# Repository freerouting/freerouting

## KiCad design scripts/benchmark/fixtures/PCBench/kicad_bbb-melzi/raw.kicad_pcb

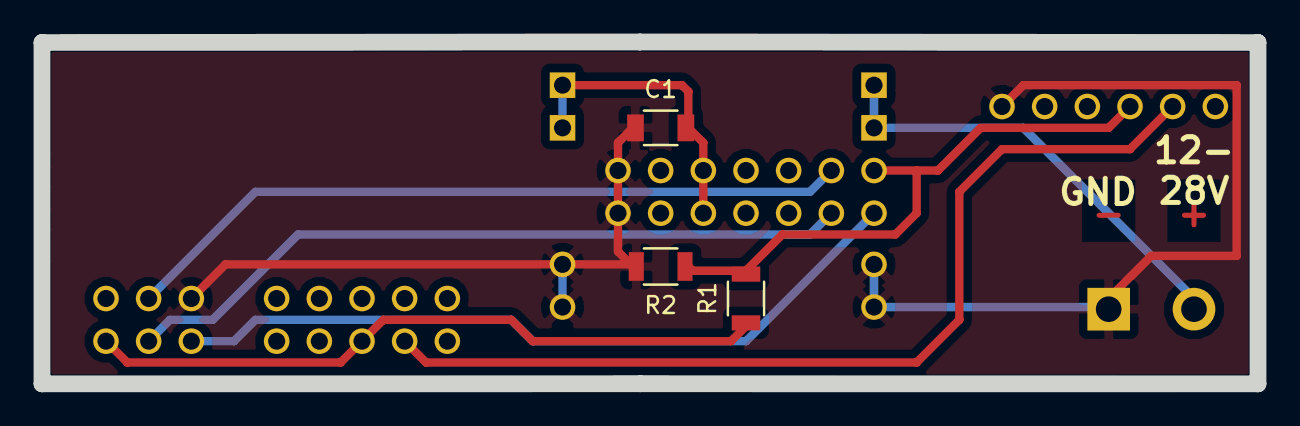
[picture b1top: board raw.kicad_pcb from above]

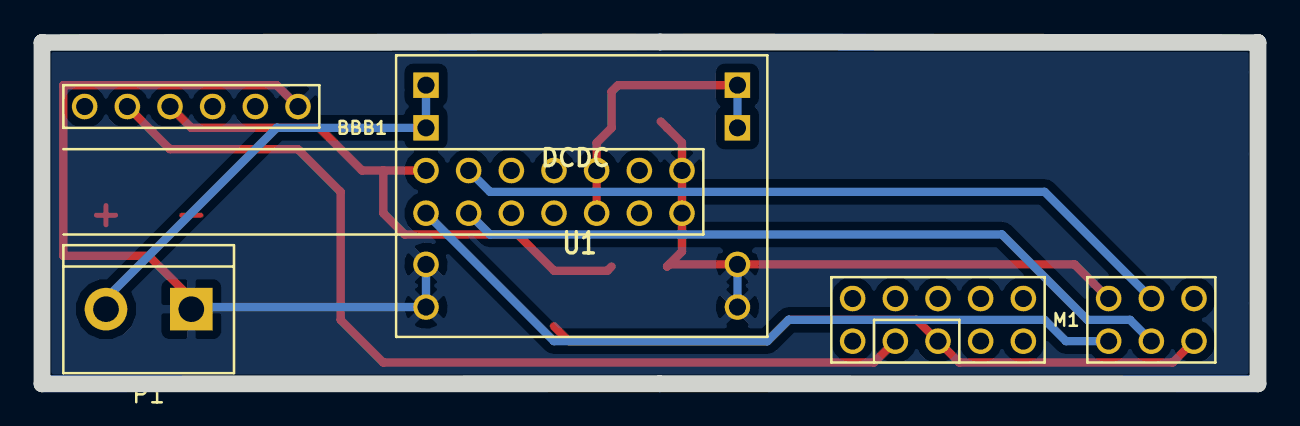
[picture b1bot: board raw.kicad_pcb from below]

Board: 2 copper layers, 72.4 x 20.4 mm, 7 parts (4 on the bottom side), 9 nets.

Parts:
BBB1: BBB
C1: C; C_1206
M1: MELZI; Melzi
P1: CONN_2; bornier2
R1, R2: R; R_1206
U1: DCDC

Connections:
/GND: BBB1.GND, C1.1, M1.GND, P1.1, R2.2, U1.GND, U1.GND2
/MISO: M1.MISO, M1.TxD, R1.1
/MISO3: BBB1.50, BBB1.RxD, R1.2, R2.1
/MOSI: BBB1.60, M1.MOSI
/Reset: BBB1.31, M1.~RST
/SCK: BBB1.30, M1.SCK
/VDD: BBB1.VDD, C1.2, U1.Vout
/VIN: P1.2, U1.Vin
unnamed: BBB1.TxD, M1.RxD

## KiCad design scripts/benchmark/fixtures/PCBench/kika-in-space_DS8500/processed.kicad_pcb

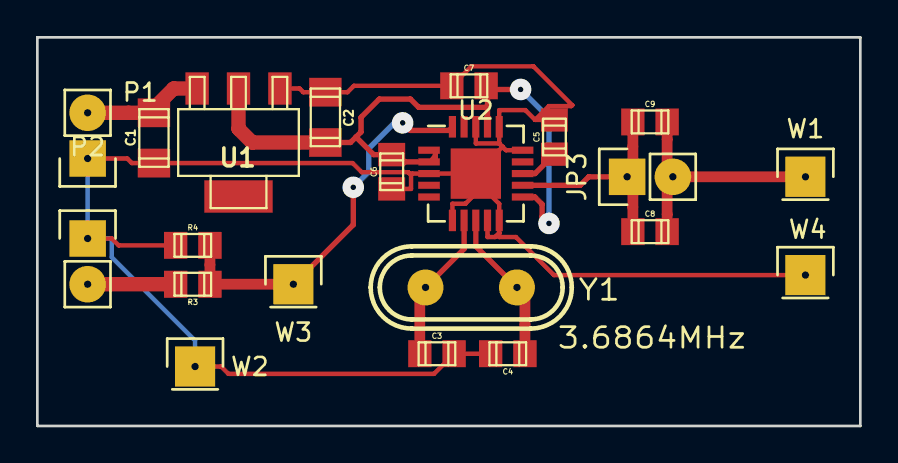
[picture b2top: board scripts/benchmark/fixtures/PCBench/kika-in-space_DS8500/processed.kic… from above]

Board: 2 copper layers, 45.7 x 21.6 mm, 21 parts (0 on the bottom side), 10 nets.

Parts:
C1, C2: 1u; c_1206
C3, C4: 22p; c_0805
C5, C6, C7, C8, C9: 100n; c_0805
JP3: Pin_Header_Straight_1x02
P1: POWER; Pin_Header_Straight_1x02
P2: INTERFACE; Pin_Header_Straight_1x02
R3: 10k; r_0805
R4: 20k; r_0805
U1: AP1117V5; sot223
U2: DS8500; QFN-20-1EP_5x5mm_Pitch0.65mm
W1: FSK_OUT; Pin_Header_Straight_1x01
W2, W4: GND; Pin_Header_Straight_1x01
W3: FSK_IN; Pin_Header_Straight_1x01
Y1: 3.6864MHz; crystal_hc-49u

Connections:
+5V: C1.1, P1.2, U1.3
GND: C1.2, C2.2, C3.1, C4.1, C5.1, C6.2, C7.2, P1.1, P2.1, R4.2, U1.1, U2.3, U2.6, U2.9, U2.10, U2.15, U2.16, U2.18, U2.21, W2.1, W4.1
unnamed: C3.2, U2.7, Y1.2
unnamed: C4.2, U2.8, Y1.1
unnamed: C5.2, U2.13
unnamed: C8.1, C9.1, JP3.2, W1.1
unnamed: C8.2, C9.2, JP3.1, U2.12
unnamed: P2.2, R3.1
unnamed: R3.2, R4.1, U2.20, W3.1
VCC: C2.1, C6.1, C7.1, U1.2, U2.1, U2.2, U2.11, U2.17

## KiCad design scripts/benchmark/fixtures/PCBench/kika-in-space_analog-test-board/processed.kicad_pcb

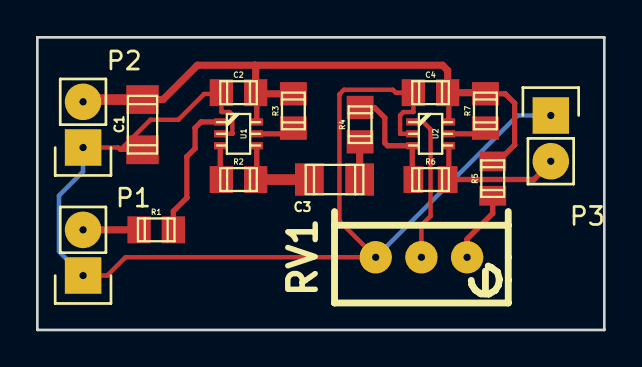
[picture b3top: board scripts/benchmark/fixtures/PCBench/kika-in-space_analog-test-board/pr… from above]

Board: 2 copper layers, 31.5 x 16.3 mm, 17 parts (0 on the bottom side), 13 nets.

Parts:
C1: 1u; c_1206
C2, C4: 100n; c_0805
C3: >1u; c_1206
P1: SIG_IN; Pin_Header_Straight_1x02
P2: POWER; Pin_Header_Straight_1x02
P3: SIG_OUT; Pin_Header_Straight_1x02
R1, R2, R6: 10k; r_0805
R3, R7: 0; r_0805
R4: 1k; r_0805
R5: 470; r_0805
RV1: 1k; Potentiometer_Bourns_3296W_3-8Zoll_Inline_ScrewUp
U1, U2: MAX9617; sc70-6

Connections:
+5V: C1.1, C2.1, C4.1, P2.2, R3.1, R5.1, R7.1, U1.6, U2.6
GND: C1.2, C2.2, C4.2, P1.1, P2.1, P3.1, RV1.3, U1.2, U2.2
unnamed: C3.1, R2.1, U1.4
unnamed: C3.2, R4.2
unnamed: P1.2, R1.2
unnamed: P3.2, R6.1, U2.4
unnamed: R1.1, U1.1
unnamed: R2.2, U1.3
unnamed: R3.2, U1.5
unnamed: R4.1, R6.2, U2.3
unnamed: R5.2, RV1.1
unnamed: R7.2, U2.5
unnamed: RV1.2, U2.1
